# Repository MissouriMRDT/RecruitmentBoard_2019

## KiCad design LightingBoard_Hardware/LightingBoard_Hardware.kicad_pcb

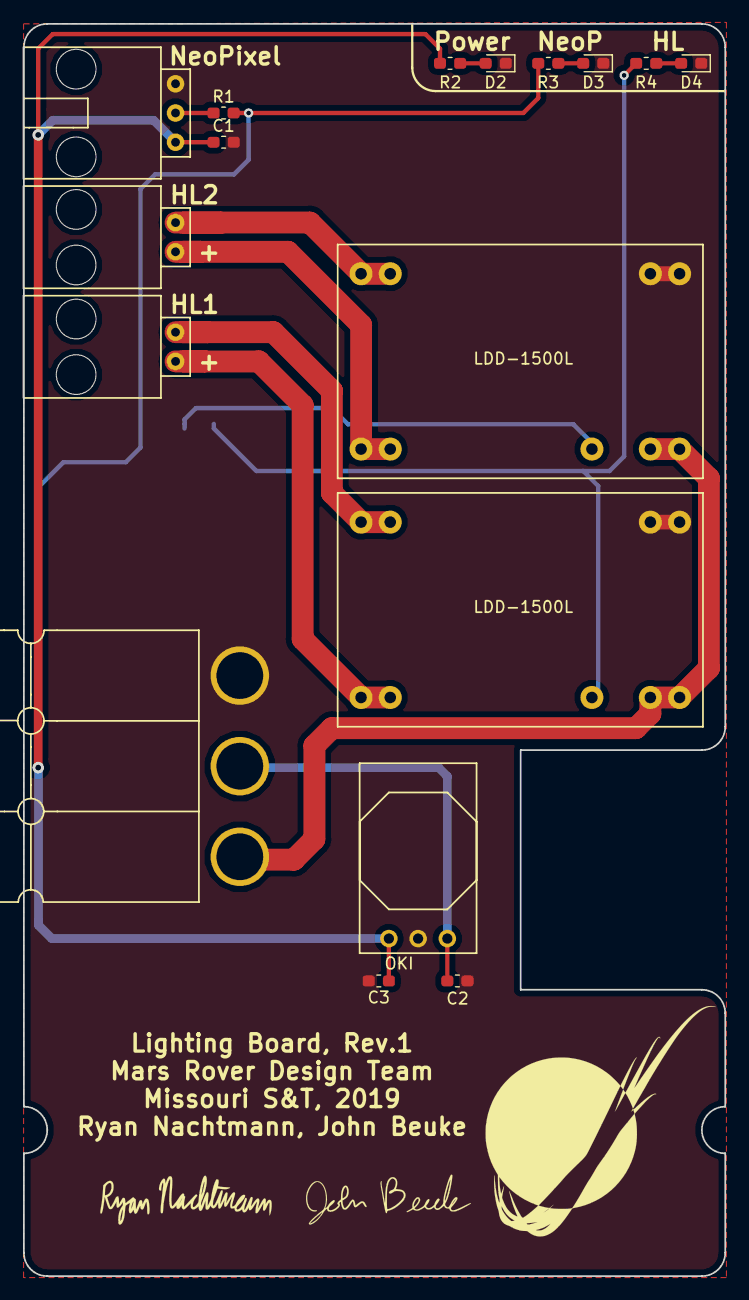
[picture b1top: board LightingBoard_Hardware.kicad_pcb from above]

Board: 2 copper layers, 61.0 x 108.8 mm, 18 parts (0 on the bottom side), 15 nets.

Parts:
C1, C2, C3: 10uF; C_0603_1608Metric_Pad1.05x0.95mm_HandSolder
Conn1: AndersonPP; Anderson_3_Horizontal_Side_by_Side
Conn2, Conn3: Molex_SL_02; MOLEX_SL_02_Horizontal
Conn4: Molex_SL_03; MOLEX_SL_03_Horizontal
D2: G_LED; LED_0603_1608Metric_Pad1.05x0.95mm_HandSolder
D3, D4: Org_LED; LED_0603_1608Metric_Pad1.05x0.95mm_HandSolder
R1: 470; R_0603_1608Metric_Pad1.05x0.95mm_HandSolder
R2, R3, R4: 500; R_0603_1608Metric_Pad1.05x0.95mm_HandSolder
U1, U2: LDD-1500L; LDD-1500L_LED_DRIVER
U3: TM4C129E_Launchpad; TM4C129E_Launchpad_X9_SMD_BOTTOM
U4: OKI; OKI_Horizontal

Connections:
+5V: C1.1, C3.1, Conn4.1, R2.1, U3.+5V, U4.3
+12VA: Conn1.3, U1.23, U1.24, U2.23, U2.24
/Headlight_V1+: Conn2.1, U1.13, U1.14
/Headlight_V1-: Conn2.2, U1.11, U1.12
/Headlight_V2+: Conn3.1, U2.13, U2.14
/Headlight_V2-: Conn3.2, U2.11, U2.12
Dout_NeoPixel: R1.2, R3.1, U3.PF1
GND: C1.2, C2.2, C3.2, Conn1.1, Conn4.3, D2.1, D3.1, D4.1, U1.1, U1.2, U2.1, U2.2, U3.GND, U4.2
Headlight_OnOff_PWM1: R4.1, U1.21, U3.PD0
Headlight_OnOff_PWM2: U2.21, U3.PD1
unnamed: C2.1, Conn1.2, U4.1
unnamed: Conn4.2, R1.1
unnamed: D2.2, R2.2
unnamed: D3.2, R3.2
unnamed: D4.2, R4.2

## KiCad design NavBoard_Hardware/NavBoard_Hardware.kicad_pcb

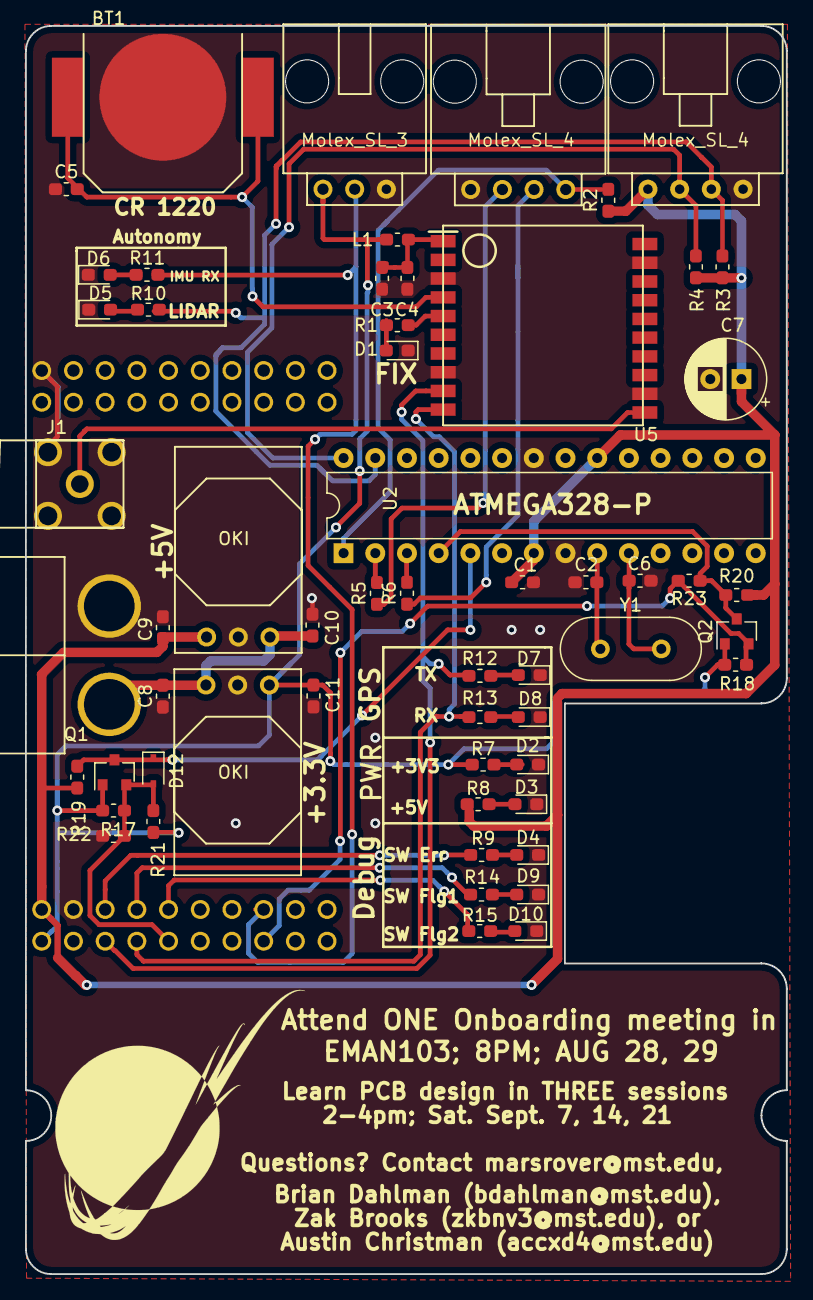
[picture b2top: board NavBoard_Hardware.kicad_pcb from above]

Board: 2 copper layers, 61.0 x 100.0 mm, 59 parts (0 on the bottom side), 37 nets.

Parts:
BT1: Battery_Cell; CR1220_Battery_Holder
C1, C3, C5: 1uF; C_0603_1608Metric_Pad1.05x0.95mm_HandSolder
C2, C6: 22pF; C_0603_1608Metric_Pad1.05x0.95mm_HandSolder
C4: 0.01uF; C_0603_1608Metric_Pad1.05x0.95mm_HandSolder
C7: 680uF; CP_Radial_D6.3mm_P2.50mm
C8, C9, C10, C11: 10u; C_0603_1608Metric_Pad1.05x0.95mm_HandSolder
Conn1: AndersonPP; Anderson_2_Horizontal_Side_by_Side
Conn2: LiDAR; MOLEX_SL_04_Horizontal
Conn3: Molex_SL_03; MOLEX_SL_03_Horizontal
Conn4: Molex_SL_04; MOLEX_SL_04_Horizontal
D1: FIX; LED_0603_1608Metric_Pad1.05x0.95mm_HandSolder
D2, D3, D4, D5, D6, D7, D8, D9, D10: LED; LED_0603_1608Metric_Pad1.05x0.95mm_HandSolder
D12: 1N4148; D_SOD-323
J1: Conn_Coaxial; RP-SMA_Jack_Tru-Hole_Right-Angle
L1: INDUCTOR; L_0603_1608Metric_Pad1.05x0.95mm_HandSolder
Q1, Q2: BSS138; SOT-23
R1, R5, R6: 1K; R_0603_1608Metric_Pad1.05x0.95mm_HandSolder
R2, R17, R18, R19, R20, R21: 10K; R_0603_1608Metric_Pad1.05x0.95mm_HandSolder
R3, R4: 4.7K; R_0603_1608Metric_Pad1.05x0.95mm_HandSolder
R7, R8, R9, R10, R11, R12, R13, R14, R15: 500; R_0603_1608Metric_Pad1.05x0.95mm_HandSolder
R22: 30K; R_0603_1608Metric_Pad1.05x0.95mm_HandSolder
R23: 0; R_0603_1608Metric_Pad1.05x0.95mm_HandSolder
U1: TM4C129E_Launchpad_X9_THT_BOTTOM
U2: ATMEGA328P-Project_Library; DIP-28_W7.62mm
U3, U4: OKI; OKI_Horizontal
U5: FGPMMOPA6H
Y1: Crystal; Crystal_HC49-U_Vertical

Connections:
+3V3: C11.1, Conn3.1, L1.1, Q1.1, Q2.1, R7.1, R17.1, R18.1, R21.1, U1.+3V3, U4.3
+5V: C1.1, C7.1, C9.1, Conn2.1, R2.1, R3.1, R4.2, R8.1, R19.1, R20.1, U1.+5V, U2.7, U2.20, U3.3
/EXAnt: J1.1, U5.11
ATM_RX: Q2.3, R20.2, R23.1, U2.4
ATM_TX: D12.1, Q1.3, R19.2, U2.5
Error_LED: R9.1, U1.PE0
GND: BT1.2, C1.2, C2.2, C3.1, C4.1, C5.2, C6.2, C7.2, C8.2, C9.2, C10.2, C11.2, Conn1.1, Conn2.4, Conn3.3, Conn4.1, D1.1, D2.1, D3.1, D4.1, D5.1, D6.1, D7.1, D8.1, D9.1, D10.1, J1.2, R22.2, U1.GND, U2.8, U2.22, U3.2, U4.2, U5.3, U5.8, U5.12, U5.19
GPS_RX: R12.1, U1.PC4, U5.9
GPS_TX: R13.1, U1.PC5, U5.10
IMU_RX: Conn3.2, R11.1, U1.PA6
LIDAR_SCL: Conn2.2, R4.1, U2.28
LIDAR_SDA: Conn2.3, R3.2, R10.1, U2.27
unnamed: C2.1, U2.9, Y1.1
unnamed: C3.2, C4.2, L1.2, U5.1
unnamed: C6.1, U2.10, Y1.2
unnamed: C8.1, C10.1, Conn1.2, U3.1, U4.1
unnamed: D1.2, R1.2
unnamed: D2.2, R7.2
unnamed: D3.2, R8.2
unnamed: D4.2, R9.2
unnamed: D5.2, R10.2
unnamed: D6.2, R11.2
unnamed: D7.2, R12.2
unnamed: D8.2, R13.2
unnamed: D9.2, R14.2
unnamed: D10.2, R15.2
unnamed: R1.1, U5.5
unnamed: R5.2, U2.2
unnamed: R6.2, U2.3
Programming_RX: Conn4.2, R5.1
Programming_TX: Conn4.3, R6.1
RESET: Conn4.4, R2.2, U2.1
SW_Flg1: R14.1, U1.PE1
SW_Flg2: R15.1, U1.PE2
TIVA_RX: D12.2, Q1.2, R17.2, R21.2, R22.1, U1.PC6
TIVA_TX: Q2.2, R18.2, R23.2, U1.PC7
VBACKUP: BT1.1, C5.1, U5.4

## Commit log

2019-07-24 Copied Files over
2019-07-27 Added dates and what not
2019-07-28 Readjusted silk screen
2019-07-28 Added notes
2019-07-29 changed size of silk
2019-07-29 More silkscreen changes
2019-07-31 Sleight silkscreen change
2019-08-01 Changed Dahls email
2019-08-02 revision 1
    made some text changes
2019-08-02 rev2
2019-08-02 final revision
2019-08-02 money
2019-08-03 magic baby
2019-08-03 small updates
